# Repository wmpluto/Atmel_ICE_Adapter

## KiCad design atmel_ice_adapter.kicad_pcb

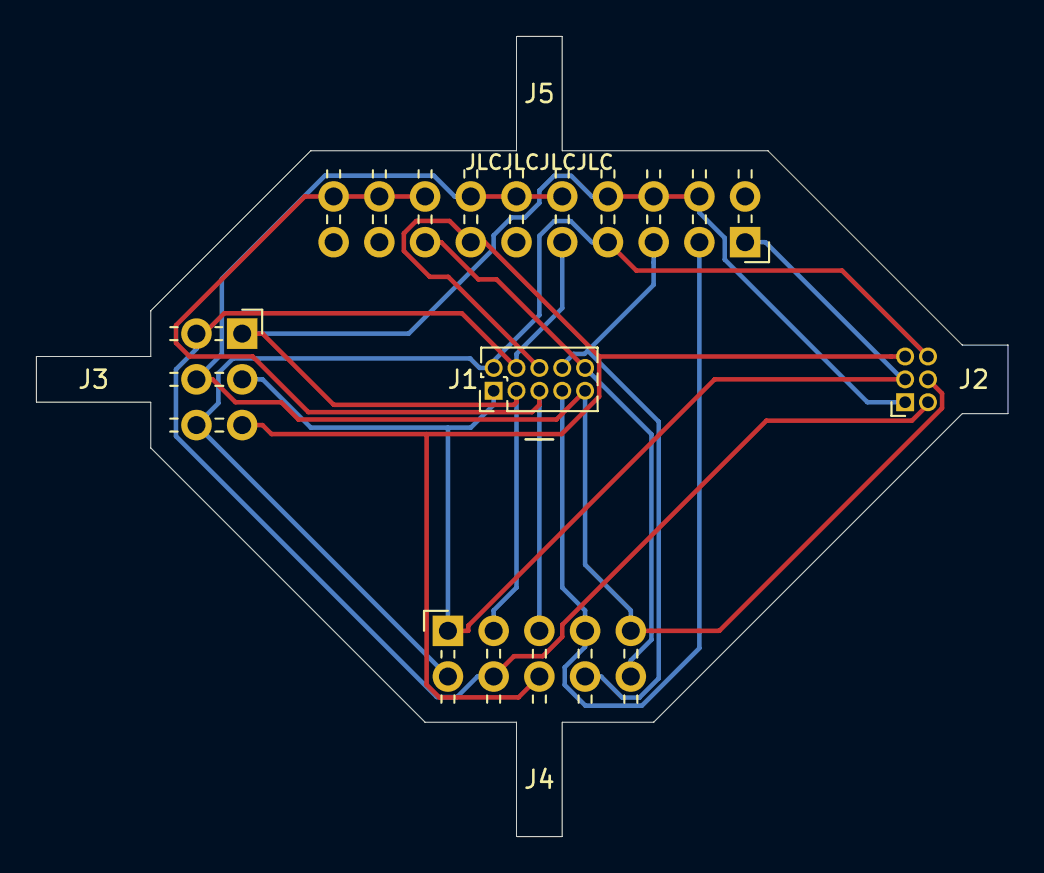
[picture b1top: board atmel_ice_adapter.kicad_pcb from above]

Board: 2 copper layers, 54.0 x 44.5 mm, 5 parts (0 on the bottom side), 10 nets.

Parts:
J1: Conn_02x05_Odd_Even; PinHeader_2x05_P1.27mm_Vertical
J2: Conn_02x03_Odd_Even; PinSocket_2x03_P1.27mm_Horizontal
J3: Conn_02x03_Odd_Even; PinSocket_2x03_P2.54mm_Horizontal
J4: Conn_02x05_Odd_Even; PinSocket_2x05_P2.54mm_Horizontal
J5: Conn_02x10_Odd_Even; PinSocket_2x10_P2.54mm_Horizontal

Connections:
/PIN1: J1.1, J2.3, J3.3, J4.1, J5.1
/PIN2: J1.2, J2.6, J3.6, J4.2, J5.7
/PIN3: J1.3, J2.1, J3.1, J4.3, J5.4, J5.6, J5.8
/PIN4: J1.4, J2.2, J3.2, J4.4, J5.9
/PIN5: J1.5, J4.5, J5.16, J5.18, J5.20
/PIN6: J1.6, J2.5, J3.5, J4.6, J5.13
/PIN7: J1.7, J4.7, J5.3
/PIN8: J1.8, J4.8, J5.5
/PIN9: J1.9, J2.4, J3.4, J4.9, J5.10, J5.12, J5.14
/PIN10: J1.10, J4.10, J5.15

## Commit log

2020-09-02 update foot print & layout
2020-09-02 update layout
2020-09-03 auto routing
2020-09-03 modify footprint
